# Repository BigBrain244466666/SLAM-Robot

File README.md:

# SLAM-Robot
A robot that uses cameras to map out a given area then is able to go to anywhere directed on the created map.

I decided to make this project as being able to map out a room seemed really cool. I also saw a video on how newer cars could implement lidar technology for auto driving, and I found that very cool and wanted to try it out.

CAD

PCB

Schematic

BOM

| Item                         | Description  | Quantity | URL                                                                                                                                                                                                                                                                                                                                                                                                                                                                                                                                                                                                                                                                                                                                                                                    | Unit Price | Total Price |
|------------------------------|--------------|----------|----------------------------------------------------------------------------------------------------------------------------------------------------------------------------------------------------------------------------------------------------------------------------------------------------------------------------------------------------------------------------------------------------------------------------------------------------------------------------------------------------------------------------------------------------------------------------------------------------------------------------------------------------------------------------------------------------------------------------------------------------------------------------------------|------------|-------------|
| Raspberry Pi 4 Model B/4GB   | SBC          |        1 | https://www.pishop.ca/product/raspberry-pi-4-model-b-4gb/                                                                                                                                                                                                                                                                                                                                                                                                                                                                                                                                                                                                                                                                                                                              |     $79.95 |  CAD $79.95 |
| ESP32 Wroom E DevKitC        | MCU          |        1 | https://www.aliexpress.com/w/wholesale-esp32-wroom-32e-dev-kit-c.html?spm=a2g0o.productlist.search.0                                                                                                                                                                                                                                                                                                                                                                                                                                                                                                                                                                                                                                                                                   |      $5.00 |   CAD $5.00 |
| RPLIDAR C1                   | LIDAR        |        1 | https://www.aliexpress.com/item/1005007924559594.html?pdp_npi=6%40dis%21CAD%21C%24101.64%21C%2469.74%21%21%21%21%21%40210328d417638404182941944e4c96%2112000042867298850%21btfpre%21%21%21%211%210%21&afTraceInfo=1005007924559594__pc__c_ppc_item_bridge_pc_main__VfP81LA__1763840418395                                                                                                                                                                                                                                                                                                                                                                                                                                                                                              |    $101.64 | CAD $101.64 |
| BNO055                       | IMU          |        1 | https://www.aliexpress.com/item/1005005499172228.html?spm=a2g0o.productlist.main.1.3a901ccfExsmif&algo_pvid=48153711-7204-4f8d-944a-19330b69eedc&algo_exp_id=48153711-7204-4f8d-944a-19330b69eedc-0&pdp_ext_f=%7B%22order%22%3A%22459%22%2C%22eval%22%3A%221%22%2C%22fromPage%22%3A%22search%22%7D&pdp_npi=6%40dis%21CAD%2111.39%214.18%21%21%217.90%212.90%21%4021032f3717638369125423194eedc0%2112000050014179039%21sea%21CA%216070736176%21ACX%211%210%21n_tag%3A-29919%3Bd%3Ae5841130%3Bm03_new_user%3A-29894%3BpisId%3A5000000190291083&curPageLogUid=UihSapAZpQX3&utparam-url=scene%3Asearch%7Cquery_from%3A%7Cx_object_id%3A1005005499172228%7C_p_origin_prod%3A#nav-specification                                                                                              |     $11.39 |  CAD $11.39 |
| DRV8871                      | Motor Driver |        2 | https://www.adafruit.com/product/3190                                                                                                                                                                                                                                                                                                                                                                                                                                                                                                                                                                                                                                                                                                                                                  |      $7.50 |  CAD $15.00 |
| JGA25-370B                   | Motors       |        2 | https://www.amazon.ca/Encoder-Magnetic-Gearbox-Reducing-Complete/dp/B07X5P1584/ref=asc_df_B07X5P1584?mcid=2a41cda6b8993377858763f13001feaf&tag=googleshopc0c-20&linkCode=df0&hvadid=730947122624&hvpos=&hvnetw=g&hvrand=443103383020499116&hvpone=&hvptwo=&hvqmt=&hvdev=c&hvdvcmdl=&hvlocint=&hvlocphy=9001032&hvtargid=pla-1949760446346&psc=1&hvocijid=443103383020499116-B07X5P1584-&hvexpln=0&gad_source=1                                                                                                                                                                                                                                                                                                                                                                         |     $21.85 |  CAD $43.70 |
| Lipo 3000mAh 3S with charger | Battery      |        1 | https://www.amazon.ca/AMZZN-Charging-Remote-Controlled-Quadcopters-Batteries/dp/B0CRRCN3XQ/ref=asc_df_B0CRRCN3XQ?mcid=81dc0417caf4372ca04e575a898ed0fe&tag=googleshopc0c-20&linkCode=df0&hvadid=730947122624&hvpos=&hvnetw=g&hvrand=11951332341292053884&hvpone=&hvptwo=&hvqmt=&hvdev=c&hvdvcmdl=&hvlocint=&hvlocphy=9001027&hvtargid=pla-2349617033680&psc=1&hvocijid=11951332341292053884-B0CRRCN3XQ-&hvexpln=0&gad_source=1                                                                                                                                                                                                                                                                                                                                                         |     $29.39 |  CAD $29.39 |
| Mini360                      | Power Board  |        1 | https://www.aliexpress.com/item/32952187058.html?spm=a2g0o.productlist.main.4.72aa6266BRkXdF&aem_p4p_detail=202511221137311226653848080880001789216&algo_pvid=ca385d34-9f19-4ee8-9165-a7e42a9202e4&algo_exp_id=ca385d34-9f19-4ee8-9165-a7e42a9202e4-3&pdp_ext_f=%7B%22order%22%3A%2216%22%2C%22eval%22%3A%221%22%2C%22fromPage%22%3A%22search%22%7D&pdp_npi=6%40dis%21CAD%215.17%211.64%21%21%213.59%211.14%21%402103212317638402511563958e89cf%2166340388582%21sea%21CA%216070736176%21ACX%211%210%21n_tag%3A-29919%3Bd%3Ae5841130%3Bm03_new_user%3A-29894%3BpisId%3A5000000190291083&curPageLogUid=dKwqC2KFxR0V&utparam-url=scene%3Asearch%7Cquery_from%3A%7Cx_object_id%3A32952187058%7C_p_origin_prod%3A&search_p4p_id=202511221137311226653848080880001789216_1                   |      $5.17 |   CAD $5.17 |
| UBEC                         | Power Board  |        1 | https://www.amazon.ca/Module-Quadcopter-Airplane-Servo-Model/dp/B0D97FH1JS/ref=sr_1_5?crid=34XQUWA73ZMDH&dib=eyJ2IjoiMSJ9.m0pTxPO753NS3oDYObu-k8i6K8n9mCvKCzZOV7XtwqcZ-EKu58rngf8MVT_F6RrL6c802PRtrV-mYSLpTZKNowluJGM60d9TDm0FbDQ-BVpwAUtkW5ycyxbyqfuoy7Ot6WLBOhsZWf7IMVX1QsbQBcJ-_KgZU62Ts3i0DKEwDaD_grBo4a_mLK4sIRNRx8BlpJ6gX3oiSnUm27ype8ylAoNO4soVaBMIY-yozpkhYEBqQvp08yWHtmCrqs9hUk4UgJEkIYbqzHf2p1XMA0sW5XF7lsyCyaosf5XJ7mo0eMw.sJIV3E6SiIE0ifugBrkMiBpmMFOwc7_9k8GQzh7-KIY&dib_tag=se&keywords=ubec+5v+5a&qid=1763835716&sprefix=ubec+5v+5a%2Caps%2C274&sr=8-5                                                                                                                                                                                                                  |     $15.99 |  CAD $15.99 |
| Toggle Switch                | Switch       |        1 | https://www.amazon.ca/FULARR-Professional-Toggle-Switch-Position/dp/B07M8WCTF5/ref=sr_1_5?dib=eyJ2IjoiMSJ9.CkI_J-8cOUIlWisfm0u68smCrZbuJT-chxkXHJTiMOPHbYxAh60jJYyqHHPGeT30-uZT3zbcNNIXMqoH9kktm7qqqclgja6LjT2VMk2IDDIcAC6pITipOufy-LaQ6oN5JG_5U-u3e3FsC93ZWaGJDQsyTsnSmoqtHyxSb-b3-iTGVga_0kOpVnGOSwvdsfq7q61sqEivdL9Vvgp8cnwC1BUSJo_fprZaODnvcZp9jkNvkSzZUD2t4c79cSXHtVwUgMwEAVgYlEklr1YJOuLbZL2WhGSjdNdI1HF3il62Bj4.bhU99RwA7BHTrBaWd5BCI3bddz0d647Hr7EL8P0EEow&dib_tag=se&keywords=spst+switch&qid=1763840808&sr=8-5                                                                                                                                                                                                                                                               |      $9.99 |   CAD $9.99 |
| Fan                          | Fan          |        1 | https://www.amazon.ca/Easycargo-Raspberry-30x30x7mm-Brushless-30mmx30mmx7mm/dp/B0792BW2VH/ref=sr_1_1?crid=1HKE0EC4GDMNG&dib=eyJ2IjoiMSJ9.1hlfsYs4lcogkcHTqtU-5-aNeiuA3ihWHRP_cypGVQSY_CtiwvpGBx4fSjEVtTZlg4fVqIUVOwBkQRI4Cl8KhkNPwWhoRhaU5WZHlARLtJA-snmvcoOYkKm3L8iemkgXwn4etObVwTgNIKVs4dHBNZn4tETIY6Y4_rv7QFvIN-pu6jmj9_nmUH6QW_TKfUHYNkN0byO61AXF2SX8K2ZYVNU9EUpaRr397uJD0Nhkfap059Evh2c8WTuxpzN1DmHyzabez_lZHaEBgXLhPtvcp2h6kmVwbiubc8e4qYTFb_0.ZwFvHFLgI1AipKGIPGJG29T8zXRXLIYVc4TuDuP-MG8&dib_tag=se&keywords=fan+for+arduino&qid=1763842344&sprefix=fan+for+arduino+%2Caps%2C129&sr=8-1                                                                                                                                                                                        |     $14.95 |  CAD $14.95 |
| Non-Polar                    | Capacitor    |        1 | https://www.aliexpress.com/item/1005009605134669.html?spm=a2g0o.productlist.main.6.1d622WWT2WWTVw&aem_p4p_detail=202511221253051185516762860500001814787&algo_pvid=12e2edf0-1c3b-4a9c-b12d-508fa144e31a&algo_exp_id=12e2edf0-1c3b-4a9c-b12d-508fa144e31a-5&pdp_ext_f=%7B%22order%22%3A%22824%22%2C%22eval%22%3A%221%22%2C%22fromPage%22%3A%22search%22%7D&pdp_npi=6%40dis%21CAD%214.24%211.64%21%21%2120.93%218.12%21%402103129f17638447855573969e1b48%2112000049607955361%21sea%21CA%216070736176%21ACX%211%210%21n_tag%3A-29919%3Bd%3Ae5841130%3Bm03_new_user%3A-29894%3BpisId%3A5000000190291084&curPageLogUid=kqltKyjr4Mrw&utparam-url=scene%3Asearch%7Cquery_from%3A%7Cx_object_id%3A1005009605134669%7C_p_origin_prod%3A&search_p4p_id=202511221253051185516762860500001814787_2 |      $1.96 |   CAD $1.96 |
| Polar                        | Capacitor    |        1 | https://www.aliexpress.com/item/1005001972941061.html?spm=a2g0o.productlist.main.13.64b124d3WXZuV6&utparam-url=scene%3Asearch%7Cquery_from%3Apc_back_same_best%7Cx_object_id%3A1005001972941061%7C_p_origin_prod%3A&algo_pvid=d8d6cc62-0e9b-4197-adfe-8e863dbd494c&algo_exp_id=d8d6cc62-0e9b-4197-adfe-8e863dbd494c&pdp_ext_f=%7B%22order%22%3A%2220%22%2C%22fromPage%22%3A%22search%22%7D&pdp_npi=6%40dis%21CAD%210.76%210.62%21%21%210.53%210.43%21%402101e8f317638453395764211e530a%2112000018277886274%21sea%21CA%216070736176%21ACX%211%210%21n_tag%3A-29919%3Bd%3Ae5841130%3Bm03_new_user%3A-29894                                                                                                                                                                               |      $1.89 |   CAD $1.89 |
| Resetable Fuse               | Fuse         |        1 | https://www.aliexpress.com/item/1005005699246438.html?spm=a2g0o.productlist.main.1.7ec733c7BC97tT&algo_pvid=1b46cfd9-8ced-4970-82ba-ee9bb2aea9af&algo_exp_id=1b46cfd9-8ced-4970-82ba-ee9bb2aea9af-0&pdp_ext_f=%7B%22order%22%3A%221018%22%2C%22eval%22%3A%221%22%2C%22fromPage%22%3A%22search%22%7D&pdp_npi=6%40dis%21CAD%212.80%211.64%21%21%211.94%211.14%21%402101eede17638457990797442ed3f7%2112000034047586731%21sea%21CA%216070736176%21ACX%211%210%21n_tag%3A-29919%3Bd%3Ae5841130%3Bm03_new_user%3A-29894%3BpisId%3A5000000190291083&curPageLogUid=aKVJzE2uOVIn&utparam-url=scene%3Asearch%7Cquery_from%3A%7Cx_object_id%3A1005005699246438%7C_p_origin_prod%3A                                                                                                                |      $2.80 |   CAD $2.80 |
| Connecter                    | Battery      |        1 | https://www.aliexpress.com/item/1005009056287669.html?spm=a2g0o.productlist.main.12.328c4f32vYB5Fd&algo_pvid=7e6977ef-9fe4-4e41-b70c-251d56b86227&algo_exp_id=7e6977ef-9fe4-4e41-b70c-251d56b86227-11&pdp_ext_f=%7B%22order%22%3A%2233%22%2C%22eval%22%3A%221%22%2C%22fromPage%22%3A%22search%22%7D&pdp_npi=6%40dis%21CAD%2114.91%211.64%21%21%2173.60%218.08%21%402101d9ef17638472789591379eea25%2112000047793614089%21sea%21CA%216070736176%21ACX%211%210%21n_tag%3A-29919%3Bd%3Ae5841130%3Bm03_new_user%3A-29894%3BpisId%3A5000000190291083&curPageLogUid=LGYtD1vTTXVE&utparam-url=scene%3Asearch%7Cquery_from%3A%7Cx_object_id%3A1005009056287669%7C_p_origin_prod%3A                                                                                                              |      $1.64 |   CAD $1.64 |
| Caster Wheel                 | Wheel        |        1 | https://www.aliexpress.com/item/1005006964734550.html?spm=a2g0o.productlist.main.4.569a3217i73L1B&algo_pvid=c5fa91da-fed8-42ba-8a1c-ad5698fdfc55&algo_exp_id=c5fa91da-fed8-42ba-8a1c-ad5698fdfc55-3&pdp_ext_f=%7B%22order%22%3A%224%22%2C%22eval%22%3A%221%22%2C%22fromPage%22%3A%22search%22%7D&pdp_npi=6%40dis%21CAD%213.71%212.74%21%21%212.57%211.90%21%402101c44f17640950068385349e8246%2112000038878335067%21sea%21CA%216070736176%21ACX%211%210%21n_tag%3A-29919%3Bd%3Ae5841130%3Bm03_new_user%3A-29894&curPageLogUid=wnrN7Gbf1v6w&utparam-url=scene%3Asearch%7Cquery_from%3A%7Cx_object_id%3A1005006964734550%7C_p_origin_prod%3A                                                                                                                                              |     $10.00 |  CAD $10.00 |
|                              |              |          |                                                                                                                                                                                                                                                                                                                                                                                                                                                                                                                                                                                                                                                                                                                                                                                        |            |             |
| Subtotal                     |              |          |                                                                                                                                                                                                                                                                                                                                                                                                                                                                                                                                                                                                                                                                                                                                                                                        |            | CAD $350.46 |
| Total (with taxes)           |              |          |                                                                                                                                                                                                                                                                                                                                                                                                                                                                                                                                                                                                                                                                                                                                                                                        |            | USD $281.17 |

PCB is extra $20 but will be after components.

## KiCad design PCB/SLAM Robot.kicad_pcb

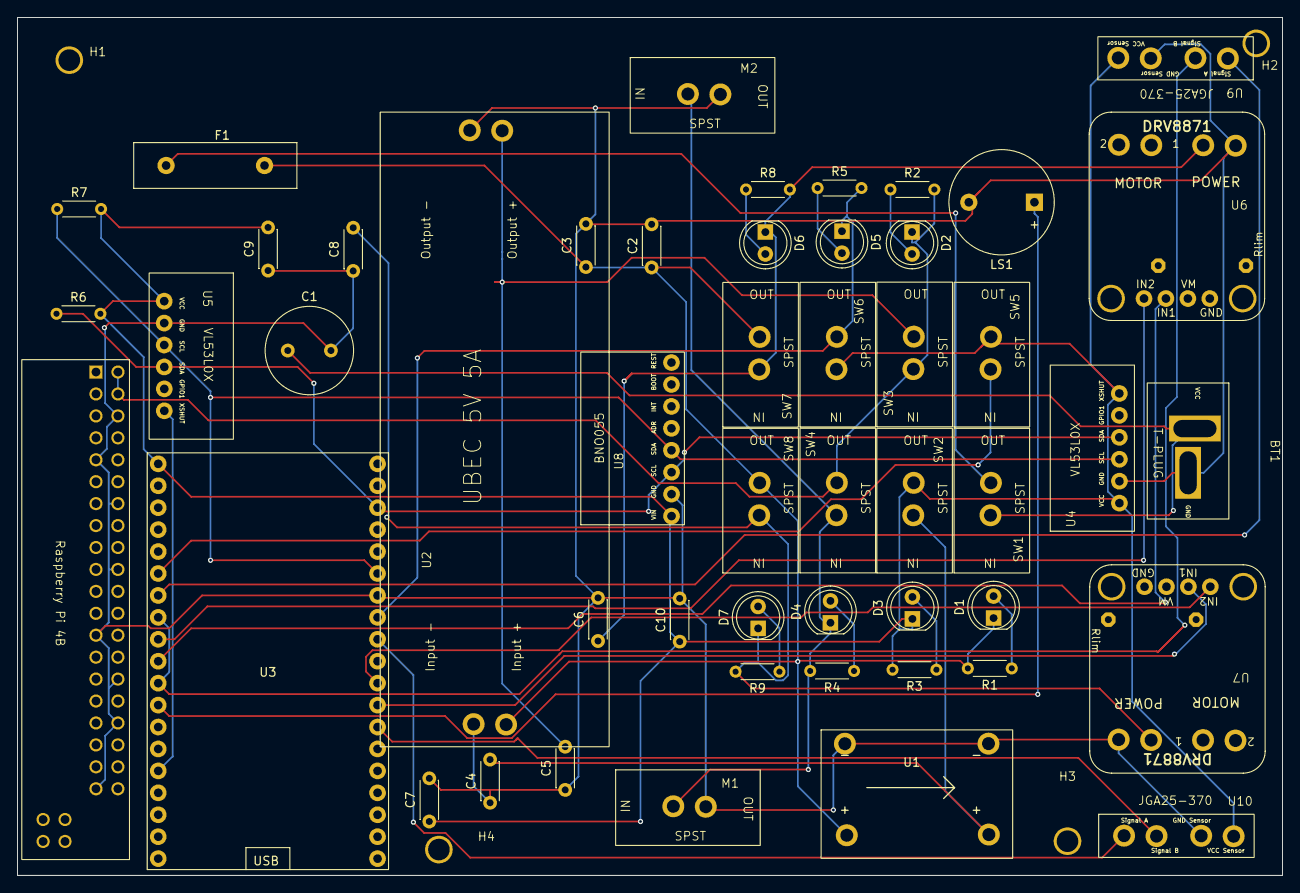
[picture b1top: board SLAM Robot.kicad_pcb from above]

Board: 2 copper layers, 146.5 x 99.4 mm, 54 parts (0 on the bottom side), 32 nets.

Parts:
BT1: LiPo 2200mAh 3S Battery; Battery T-Plug
C1: C_Polarized; C_Radial_D10.0mm_H16.0mm_P5.00mm
C2, C3, C4, C5, C6, C7, C8, C9, C10: C; C_Disc_D4.3mm_W1.9mm_P5.00mm
D1: Main LED; LED_D5.0mm
D2: 5V LED; LED_D5.0mm
D3: 3.3V LED; LED_D5.0mm
D4: Fan LED; LED_D5.0mm
D5: Bluetooth LED; LED_D5.0mm
D6: Motor 2 LED; LED_D5.0mm
D7: Motor 1 LED; LED_D5.0mm
F1: Fuse; Fuse_Littelfuse-LVR100
H1, H2, H3, H4: MountingHole; Mounting Hole
J1: Raspberry_Pi_4; MODULE_RASPBERRY_PI_4B_4GB
LS1: Speaker; Buzzer_12x9.5RM7.6
M1, M2: Fan; SPST
R1, R2, R3, R4, R5, R8, R9: 330 Ohm; R_Axial_DIN0204_L3.6mm_D1.6mm_P5.08mm_Horizontal
R6: 4.7K - 10K; R_Axial_DIN0204_L3.6mm_D1.6mm_P5.08mm_Horizontal
R7: R; R_Axial_DIN0204_L3.6mm_D1.6mm_P5.08mm_Horizontal
SW1: Main Switch; SPST
SW2: 3.3V Switch; SPST
SW3: 5V Switch; SPST
SW4: Fan Switch; SPST
SW5: Diagnostics Button; SPST
SW6: Bluetooth Switch; SPST
SW7: Motor 2 Switch; SPST
SW8: Motor 1 Switch; SPST
U1: Mini360_Module
U2: UBEC
U3: ESP32-DEVKITC
U4, U5: VL53L0X
U6, U7: DRV8871
U8: BNO055
U9, U10: JGA25-370

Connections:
+3.3V: C7.1, C9.2, C10.1, D3.1 (K), R3.2, R6.2, R7.2, SW2.2 (B), SW5.2, SW6.1 (A), U3.1 (3V3), U4.1 (VCC), U4.6 (XSHUT), U5.1 (VCC), U8.1 (VIN), U9.3 (VCC_for_Hall_Sensor), U10.3 (VCC_for_Hall_Sensor)
+5V: D2.1 (K), J1.2 (5V), J1.4 (5V), R2.2, SW3.1 (A), SW4.2 (B)
+12V: C2.1, C3.1, D1.1 (K), F1.2, R1.2, SW7.2 (B), SW8.2 (B), U1.2 (Input_+), U2.2 (Input_+)
GND: BT1.2 (-), C1.2, C2.2, C3.2, C4.1, C5.1, C6.2, C7.2, C8.1, C9.1, C10.2, J1.6 (GND), J1.9 (GND), J1.14 (GND), J1.20 (GND), J1.25 (GND), J1.30 (GND), J1.34 (GND), J1.39 (GND), LS1.2, M1.2 (-), M2.2 (-), U1.1 (Input_-), U1.3 (Output_-), U2.1 (Input_-), U2.3 (Output_-), U3.32 (GND2), U4.2 (GND), U5.2 (GND), U6.4 (Power_-), U7.4 (Power_-), U8.2 (GND), U9.4 (GND_for_Hall_Sensor), U10.4 (GND_for_Hall_Sensor)
unnamed: BT1.1 (+), C1.1, SW1.1 (A)
unnamed: D1.2 (A), R1.1
unnamed: D2.2 (A), R2.1
unnamed: D3.2 (A), R3.1
unnamed: D4.2 (A), R4.1
unnamed: D4.1 (K), M1.1 (+), M2.1 (+), R4.2, SW4.1 (A)
unnamed: D5.2 (A), R5.1
unnamed: D5.1 (K), R5.2, SW6.2 (B), U3.31 (GPIO19/SPI_MISO)
unnamed: D6.2 (A), R8.1
unnamed: C6.1, D6.1 (K), R8.2, SW7.1 (A), U6.3 (Power_+)
unnamed: D7.2 (A), R9.1
unnamed: C8.2, D7.1 (K), R9.2, SW8.1 (A), U7.3 (Power_+)
unnamed: F1.1, SW1.2 (B)
unnamed: C4.2, SW2.1 (A), U1.4 (Output_+)
unnamed: C5.2, SW3.2 (B), U2.4 (Output_+)
unnamed: U3.15 (GPIO13/AD14//TOUCH4/HSPI_MOSI), U5.6 (XSHUT)
unnamed: LS1.1, U3.12 (GPIO14/AD16/TOUCH6/HSPI_SCK)
unnamed: U3.27 (GPIO16), U7.6 (In_2)
unnamed: U3.28 (GPIO17), U7.5 (In_1)
unnamed: R7.1, U3.33 (GPIO21/WIRE_SDA), U4.3 (SCL), U5.3 (SCL), U8.4 (SDA/TX)
unnamed: R6.1, U3.36 (GPIO22/WIRE_SCL), U4.4 (SDA), U5.4 (SDA), U8.3 (SCL/RX)
unnamed: U3.9 (GPIO25/AD18/DA1), U6.5 (In_1)
unnamed: U3.10 (GPIO26/AD19/DA2), U6.6 (In_2)
unnamed: U3.8 (GPIO33/AD5/TOUCH8), U3.11 (GPIO27/AD17/TOUCH7), U9.5 (Signal-Hall_Sensor_1)
unnamed: U3.7 (GPIO32/AD4/TOUCH9), U9.6 (Signal-Hall_Sensor_2)
unnamed: SW5.1, U3.6 (GPIO35/AD7)
unnamed: U3.26 (GPIO4/AD10/TOUCH0), U10.5 (Signal-Hall_Sensor_1)
unnamed: U3.30 (GPIO18/SPI_CLK), U10.6 (Signal-Hall_Sensor_2)

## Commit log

2025-11-26 Upload all local files
2025-11-26 Update README with project details and BOM
    Added detailed project description, CAD, PCB, schematic, BOM, and images for components.
2025-11-26 Add PCB cost note to README
    Added note about PCB cost being extra.
2025-12-01 Add Raspberry Pi serial commander for robot control
    This script establishes a ROS node for controlling a robot via serial communication. It translates velocity commands into wheel speeds and manages the serial connection to an ESP32.
2025-12-01 Enhance code clarity with comments and cleanup
    Added comments to clarify code functionality and removed unnecessary comments.
2025-12-01 Add ESP32 to Raspberry Pi odometry data reader
    This script reads odometry data from an ESP32 via serial and publishes it to ROS topics.
2025-12-01 Add new file raspberryPi_to_esp.py
2025-12-01 Create ROS launch file for differential drive robot
    This launch file starts the communication nodes for the differential drive robot and publishes necessary static transforms for the robot's frames.
2025-12-01 Add configuration parameters for robot costmap
